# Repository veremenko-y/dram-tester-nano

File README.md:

# DRAM Tester

Tester for 4164/41256 DRAM chips using Arduino Nano.

Based on https://github.com/Tishima/myDRAMTester, which is itself is based on https://forum.defence-force.org/viewtopic.php?t=1699

# Enclosure

Enclosure can be assembled with 4 3Mx8 socket head cap screws.

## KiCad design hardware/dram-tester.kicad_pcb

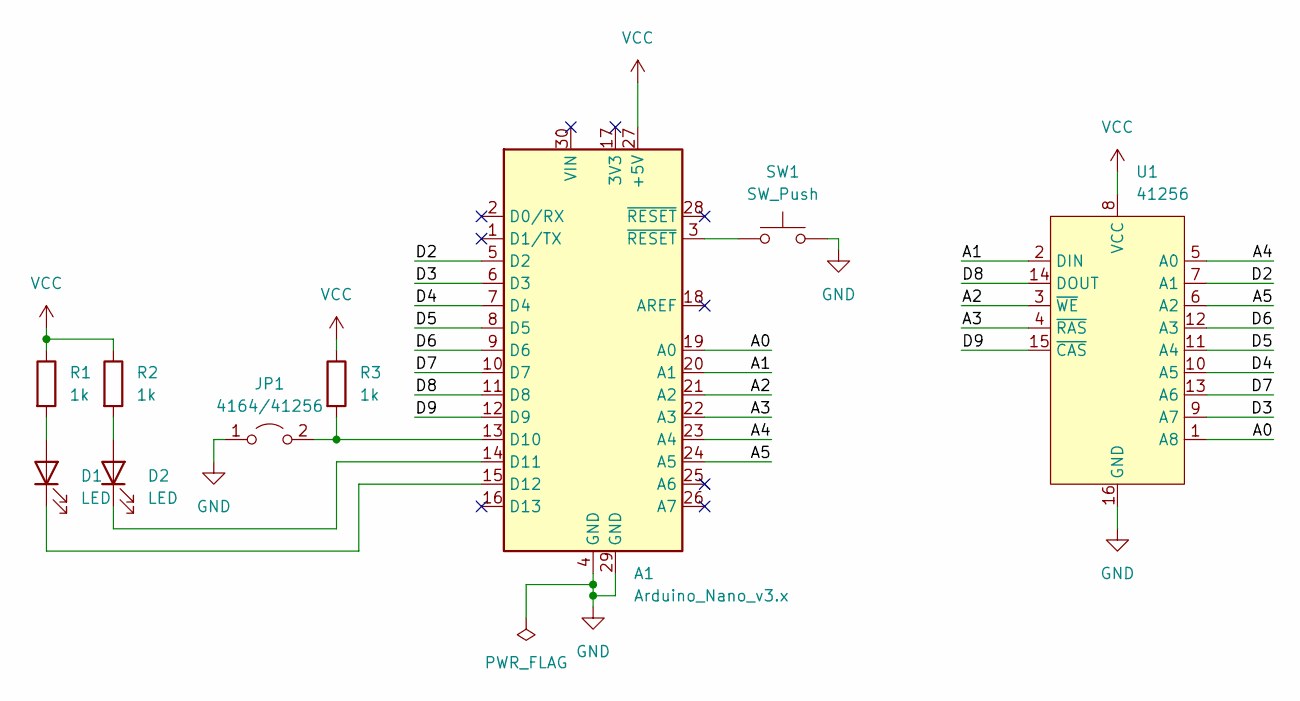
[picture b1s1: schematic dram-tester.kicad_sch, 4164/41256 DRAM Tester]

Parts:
A1: Arduino_Nano_v3.x; Arduino_Nano
D1, D2: LED; LED_D3.0mm
JP1: 4164/41256; PinHeader_1x02_P2.54mm_Vertical
R1, R2, R3: 1k; R_Axial_DIN0207_L6.3mm_D2.5mm_P2.54mm_Vertical
SW1: SW_Push; SW_PUSH_6mm
U1: 41256; 216-3340-00-0602J

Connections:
/A0: A1.19 (A0), U1.1 (A8)
/A1: A1.20 (A1), U1.2 (DIN)
/A2: A1.21 (A2), U1.3 (~WE)
/A3: A1.22 (A3), U1.4 (~RAS)
/A4: A1.23 (A4), U1.5 (A0)
/A5: A1.24 (A5), U1.6 (A2)
/D2: A1.5 (D2), U1.7 (A1)
/D3: A1.6 (D3), U1.9 (A7)
/D4: A1.7 (D4), U1.10 (A5)
/D5: A1.8 (D5), U1.11 (A4)
/D6: A1.9 (D6), U1.12 (A3)
/D7: A1.10 (D7), U1.13 (A6)
/D8: A1.11 (D8), U1.14 (DOUT)
/D9: A1.12 (D9), U1.15 (~CAS)
GND: A1.4 (GND), A1.29 (GND), JP1.1 (A), SW1.2, U1.16 (GND)
unnamed: A1.3 (~RESET), SW1.1
unnamed: A1.13 (D10), JP1.2 (B), R3.2
unnamed: A1.14 (D11), D2.1 (K)
unnamed: A1.15 (D12), D1.1 (K)
unnamed: D1.2 (A), R1.2
unnamed: D2.2 (A), R2.2
VCC: A1.27 (+5V), R1.1, R2.1, R3.1, U1.8 (VCC)

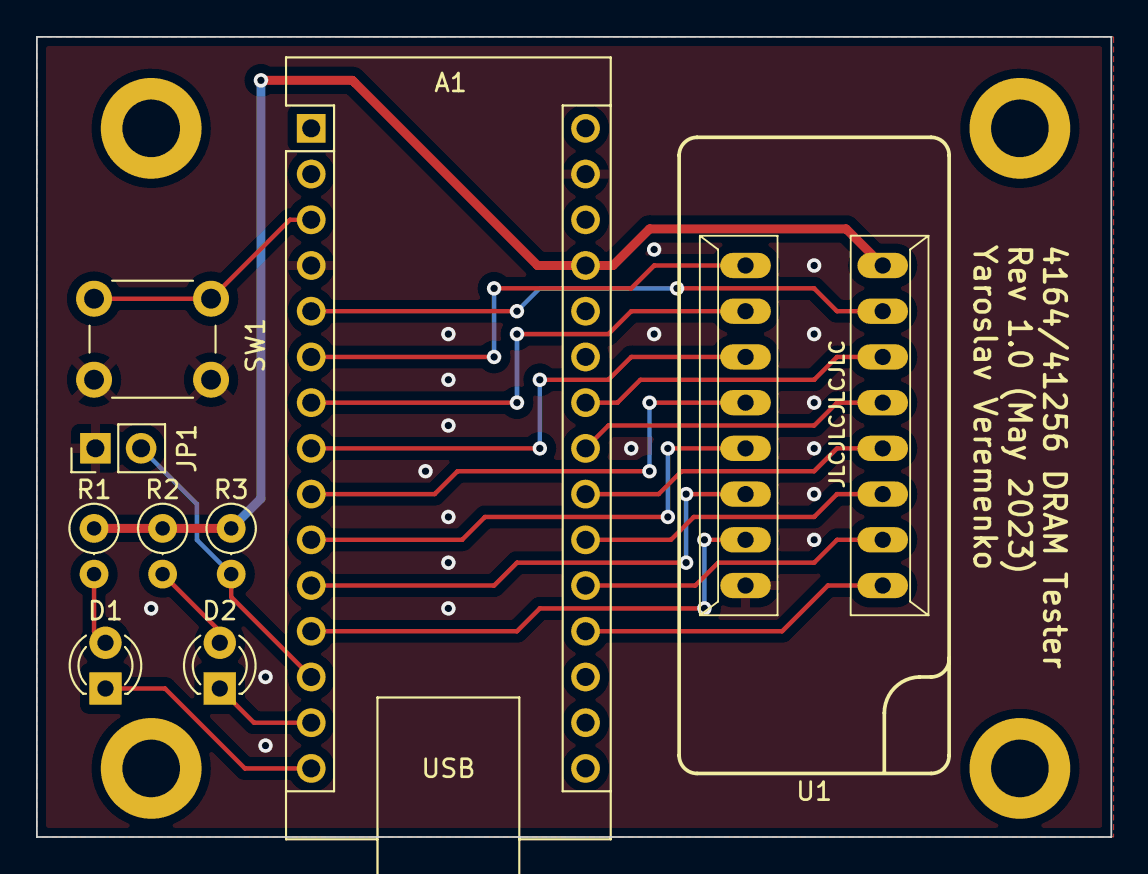
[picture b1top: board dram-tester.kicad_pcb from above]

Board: 2 copper layers, 59.7 x 44.5 mm, 9 parts (0 on the bottom side), 22 nets.

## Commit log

2023-08-03 Rev 1.0
2023-08-03 Uploaded "correct" up-to-date firmware
2024-03-31 Added STEP files for the enclosure
2024-03-31 Added 3d models for the board
2024-03-31 Updated enclosure files
2024-04-01 Added STL files for the case
